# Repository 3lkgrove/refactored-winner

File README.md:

# Race Timing Light with Remote Trigger

## **Schematic**

## **PCB**

## **Gerber Files**

Gerber files can be found [HERE](PCB/KiCAD/refactored-winner/gerber_to_order).

## Licensing

This project is licensed under the terms of the **GNU General Public License v3.0** (GPL-3.0). The full text of the license can be found in the [LICENSE](LICENSE) file in the root directory of this repository.

Copyright (c) 2026 [@3lkgrove](https://www.github.com/3lkgrove)

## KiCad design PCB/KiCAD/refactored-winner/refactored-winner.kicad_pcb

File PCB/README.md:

# Race Timing Light with Remote Trigger

**MORE COMING SOON!**

## **Schematic**

## **PCB**

## **Gerber Files**

Gerber files can be found [HERE](KiCAD/refactored-winner/gerber_to_order).

## Licensing

This project is licensed under the terms of the **GNU General Public License v3.0** (GPL-3.0). The full text of the license can be found in the [LICENSE](LICENSE) file in the root directory of this repository.

Copyright (c) 2026 [@3lkgrove](https://www.github.com/3lkgrove)

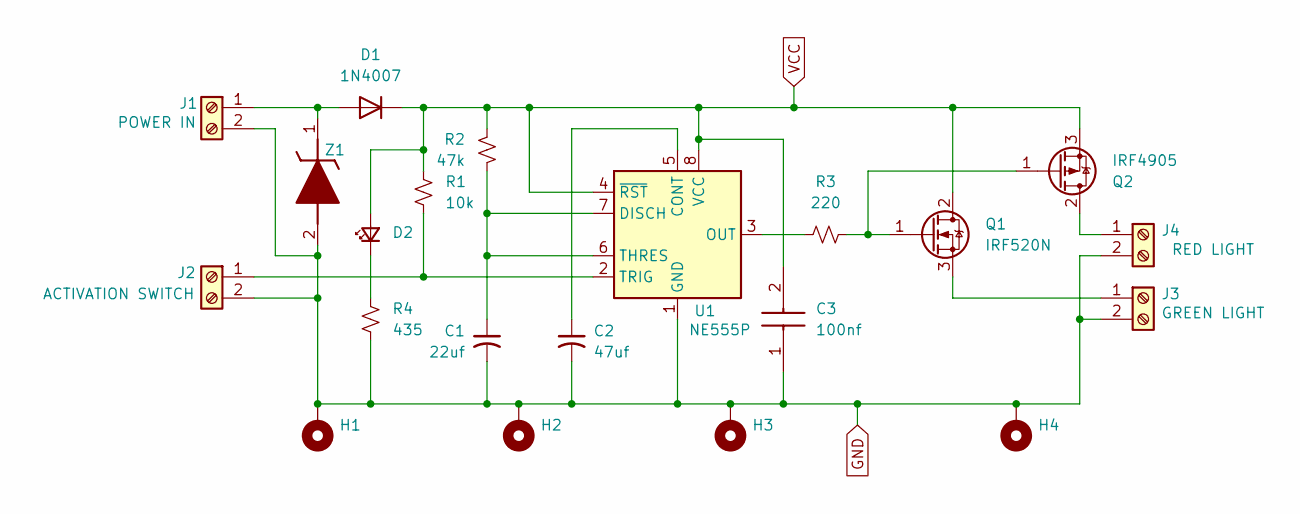
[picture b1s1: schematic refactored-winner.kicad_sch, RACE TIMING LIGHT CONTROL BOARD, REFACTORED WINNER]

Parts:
C1: 22uf; C_Radial_D5.0mm_H11.0mm_P2.00mm
C2: 47uf; C_Radial_D5.0mm_H11.0mm_P2.00mm
C3: 100nf; K104K15X7RF5UL2; Mouser Part Number 594-K104K15X7RF5UL2
D1: 1N4007; D_DO-41_SOD81_P10.16mm_Horizontal
D2: LED_Small; LED_D5.0mm_Clear
H1, H2, H3, H4: MountingHole_Pad; MountingHole_3.2mm_M3_Pad_TopBottom
J1: POWER IN; TerminalBlock_Phoenix_MKDS-1,5-2-5.08_1x02_P5.08mm_Horizont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
J2: ACTIVATION SWITCH; TerminalBlock_Phoenix_MKDS-1,5-2-5.08_1x02_P5.08mm_Horizont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
J3: GREEN LIGHT; TerminalBlock_Phoenix_MKDS-1,5-2-5.08_1x02_P5.08mm_Horizont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
J4: RED LIGHT; TerminalBlock_Phoenix_MKDS-1,5-2-5.08_1x02_P5.08mm_Horizont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
Q1: IRF520N; TO-220-3_Vertical
Q2: IRF4905; TO-220-3_Vertical
R1: 10k; R_Axial_DIN0204_L3.6mm_D1.6mm_P5.08mm_Horizontal
R2: 47k; R_Axial_DIN0204_L3.6mm_D1.6mm_P5.08mm_Horizontal
R3: 220; R_Axial_DIN0204_L3.6mm_D1.6mm_P5.08mm_Horizontal
R4: 435; R_Axial_DIN0207_L6.3mm_D2.5mm_P7.62mm_Horizontal
U1: NE555P; DIP-8_W7.62mm
Z1: BZX85C15-TAP; DIOAD1450W86L410D260; Mouser Part Number 625-BZX85C15-TAP

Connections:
GND: C1.2, C2.2, C3.1, H1.1, H2.1, H3.1, H4.1, J1.2, J2.2, J3.2, J4.2, R4.1, U1.1 (GND), Z1.2 (A)
unnamed: D1.2 (A), J1.1, Z1.1 (K)
unnamed: D2.1 (K), R4.2
unnamed: J2.1, R1.1, U1.2 (TRIG)
unnamed: J3.1, Q1.3 (S)
unnamed: J4.1, Q2.2 (D)
unnamed: Q1.1 (G), Q2.1 (G), R3.2
unnamed: C2.1, U1.5 (CONT)
unnamed: C1.1, R2.1, U1.6 (THRES), U1.7 (DISCH)
unnamed: R3.1, U1.3 (OUT)
VCC: C3.2, D1.1 (K), D2.2 (A), Q1.2 (D), Q2.3 (S), R1.2, R2.2, U1.4 (~RST), U1.8 (VCC)

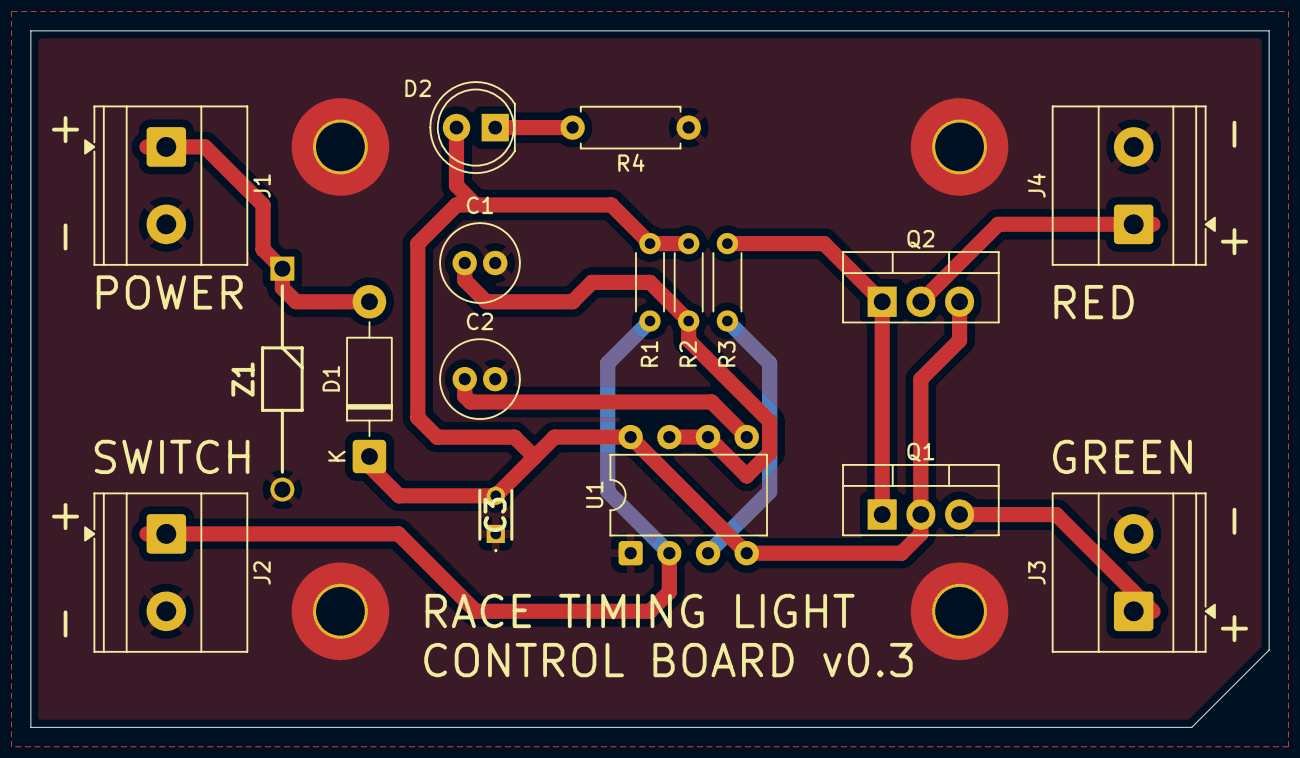
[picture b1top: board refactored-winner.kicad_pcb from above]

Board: 2 copper layers, 81.3 x 45.7 mm, 21 parts (0 on the bottom side), 11 nets.

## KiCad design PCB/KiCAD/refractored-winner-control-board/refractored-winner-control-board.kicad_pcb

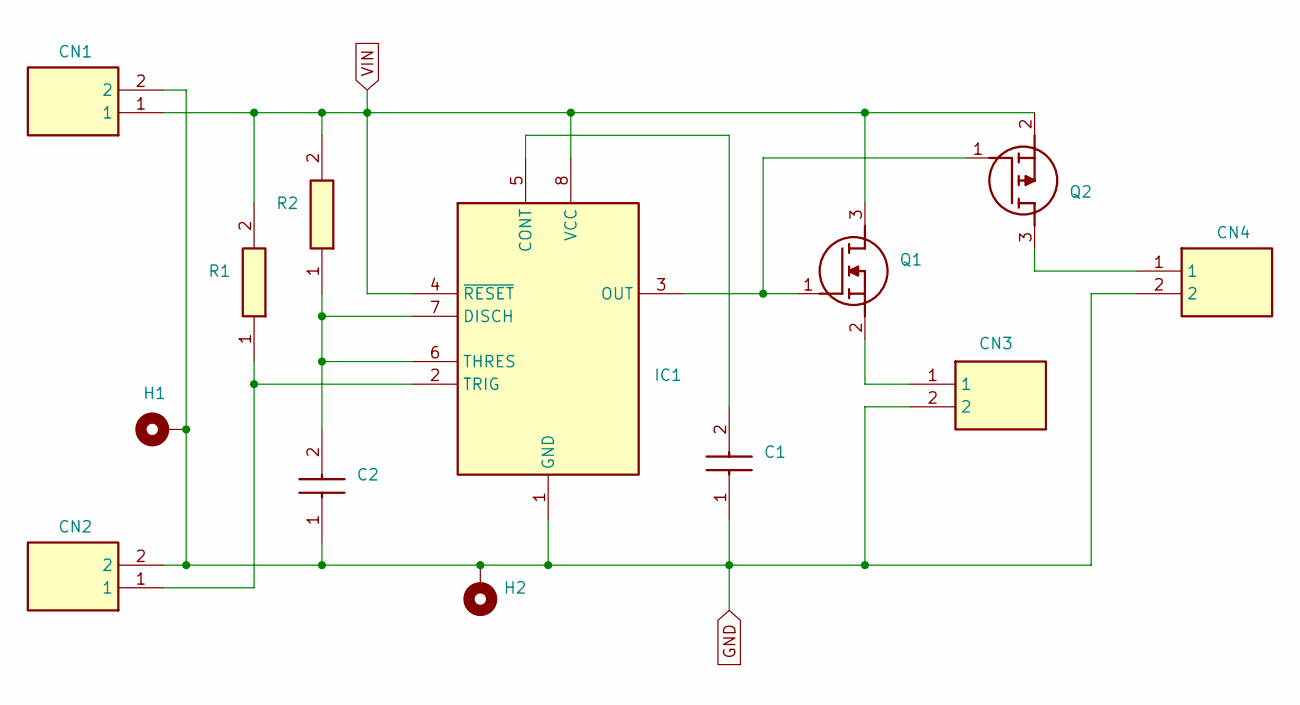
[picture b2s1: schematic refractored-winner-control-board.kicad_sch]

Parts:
C1: 12063A103JAT2A; CAPC3216X152N; Mouser Part Number 581-12063A103J
C2: 12063D226MAT2A; CAPC3216X229N; Mouser Part Number 581-12063D226MAT2A
CN1, CN2, CN3, CN4: 1716080000; Mouser Part Number 470-1716080000
H1, H2: MountingHole_Pad; MountingHole_3.2mm_M3_Pad_TopBottom
IC1: NE555DR; Manufacturer_Part_Number NE555DR; Mouser Part Number 595-NE555DR
Q1: IRLML6344TRPBF; SOT95P237X112-3N; Mouser Part Number 942-IRLML6344TRPBF
Q2: DMP3130L-7; SOT96P240X110-3N; Mouser Part Number 621-DMP3130L-7
R1: CRGCQ1206F10K; RESC3116X65N; Mouser Part Number 279-CRGCQ1206F10K
R2: CRGCQ1206F100K; RESC3116X65N; Mouser Part Number 279-CRGCQ1206F100K

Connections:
GND: C1.1, C2.1, CN1.2, CN2.2, CN3.2, CN4.2, H1.1, H2.1, IC1.1 (GND)
unnamed: C1.2, IC1.5 (CONT)
unnamed: C2.2, IC1.6 (THRES), IC1.7 (DISCH), R2.1
unnamed: IC1.3 (OUT), Q1.1 (G), Q2.1 (G)
unnamed: CN2.1, IC1.2 (TRIG), R1.1
unnamed: CN3.1, Q1.2 (S)
unnamed: CN4.1, Q2.3 (D)
VIN: CN1.1, IC1.4 (~RESET), IC1.8 (VCC), Q1.3 (D), Q2.2 (S), R1.2, R2.2

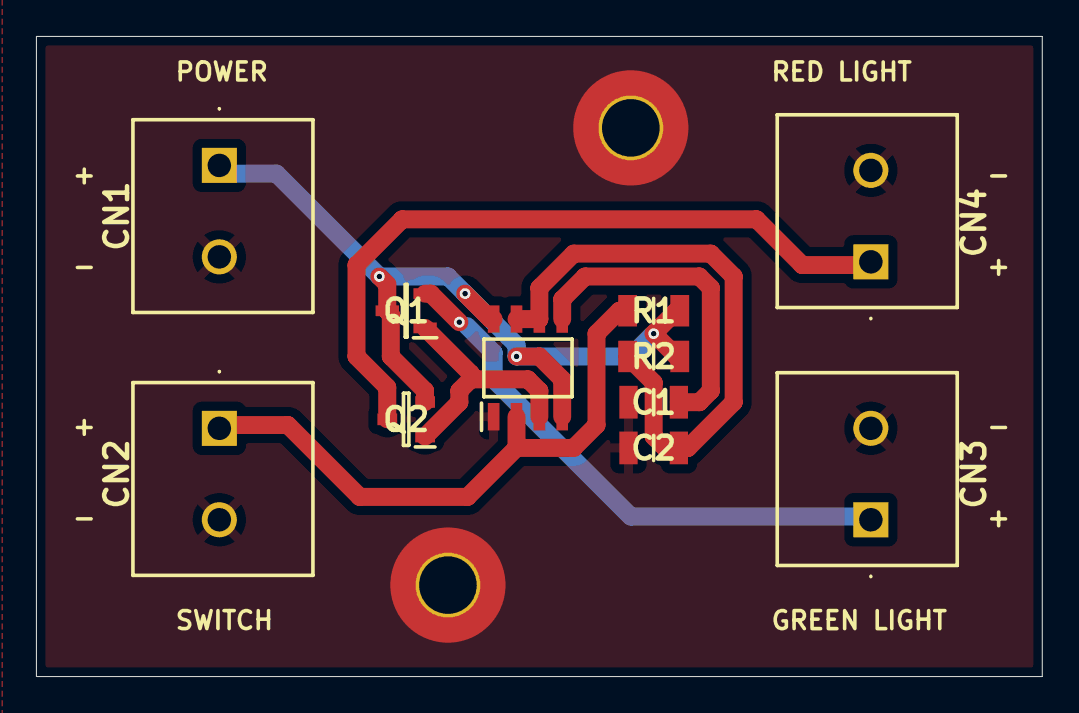
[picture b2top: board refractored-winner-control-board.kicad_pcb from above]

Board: 2 copper layers, 55.9 x 35.6 mm, 13 parts (0 on the bottom side), 8 nets.

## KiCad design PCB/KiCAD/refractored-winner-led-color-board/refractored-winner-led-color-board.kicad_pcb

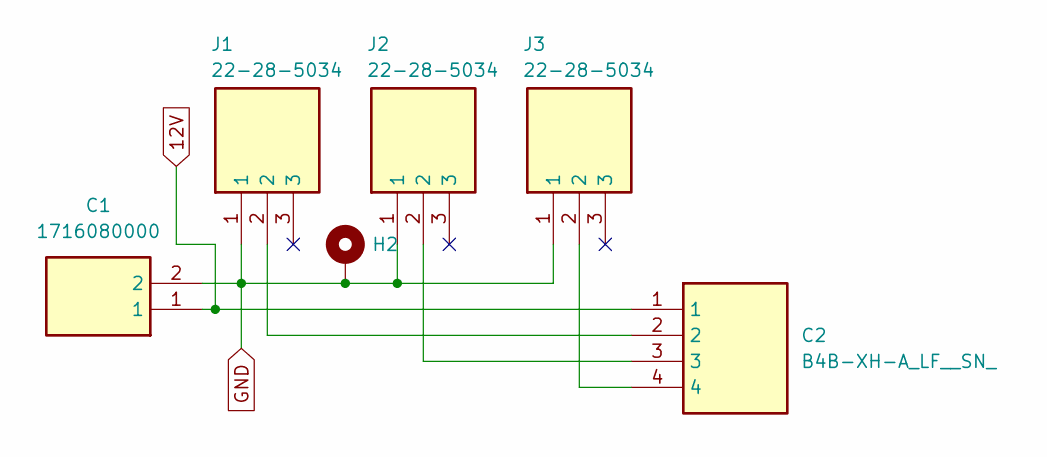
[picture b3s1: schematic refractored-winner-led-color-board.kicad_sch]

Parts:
C1: 1716080000; Mouser Part Number 470-1716080000
C2: B4B-XH-A_LF__SN_; B4BXHALFSN; Mouser Part Number 306-B4BXHALFSN
H2: MountingHole_Pad; MountingHole_3.2mm_M3_Pad_TopBottom
J1, J2, J3: 22-28-5034; HDRV3W66P0X254_1X3_1016X249X1042P; Mouser Part Number 538-22-28-5034

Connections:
12V: C1.1, C2.1
GND: C1.2, H2.1, J1.1, J2.1, J3.1
unnamed: C2.2, J1.2
unnamed: C2.3, J2.2
unnamed: C2.4, J3.2

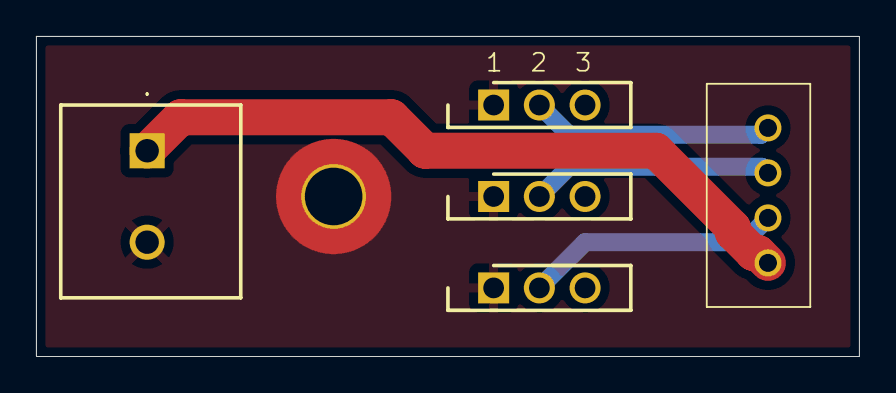
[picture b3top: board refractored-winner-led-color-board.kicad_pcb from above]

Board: 2 copper layers, 45.7 x 17.8 mm, 6 parts (0 on the bottom side), 5 nets.

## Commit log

2026-01-06 01062026-ARS-01
    BASE FOLDER STRCUTURE AND README.MD FILES
2026-01-22 01222026_ARS_01
    CREATED PCB FOR CONTROLLER
    CREATED PCB FOR LED COLOR SELECTOR
2026-02-11 02112026
2026-02-12 02122026_ARS-01
2026-02-12 02122026_ARS-02
2026-02-12 02122026_ARS-03
2026-02-12 02122026_ARS-04
